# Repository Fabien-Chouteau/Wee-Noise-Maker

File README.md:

The [PGB-1 Firmware is now hosted on a different repo](https://github.com/wee-noise-makers/WNM-PGB1-firmware).

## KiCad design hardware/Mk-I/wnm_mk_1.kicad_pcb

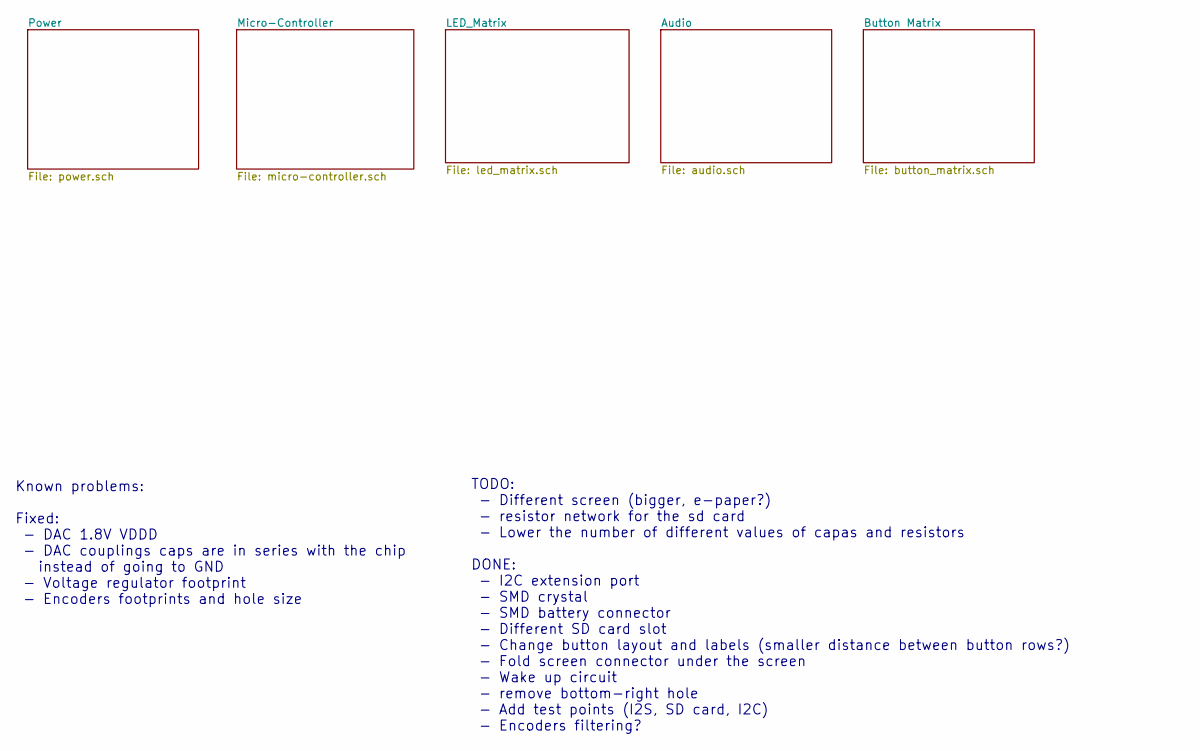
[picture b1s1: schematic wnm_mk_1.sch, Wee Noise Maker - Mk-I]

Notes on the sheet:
TODO: - Different screen (bigger, e-paper?) - resistor network for the sd card - Lower the number of different values of capas and resistors DONE: - I2C extension port - SMD crystal - SMD battery connector - Different SD card slot - Change button layout and labels (smaller distance between button r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
Known problems: Fixed: - DAC 1.8V VDDD - DAC couplings caps are in series with the chip instead of going to GND - Voltage regulator footprint - Encoders footprints and hole size

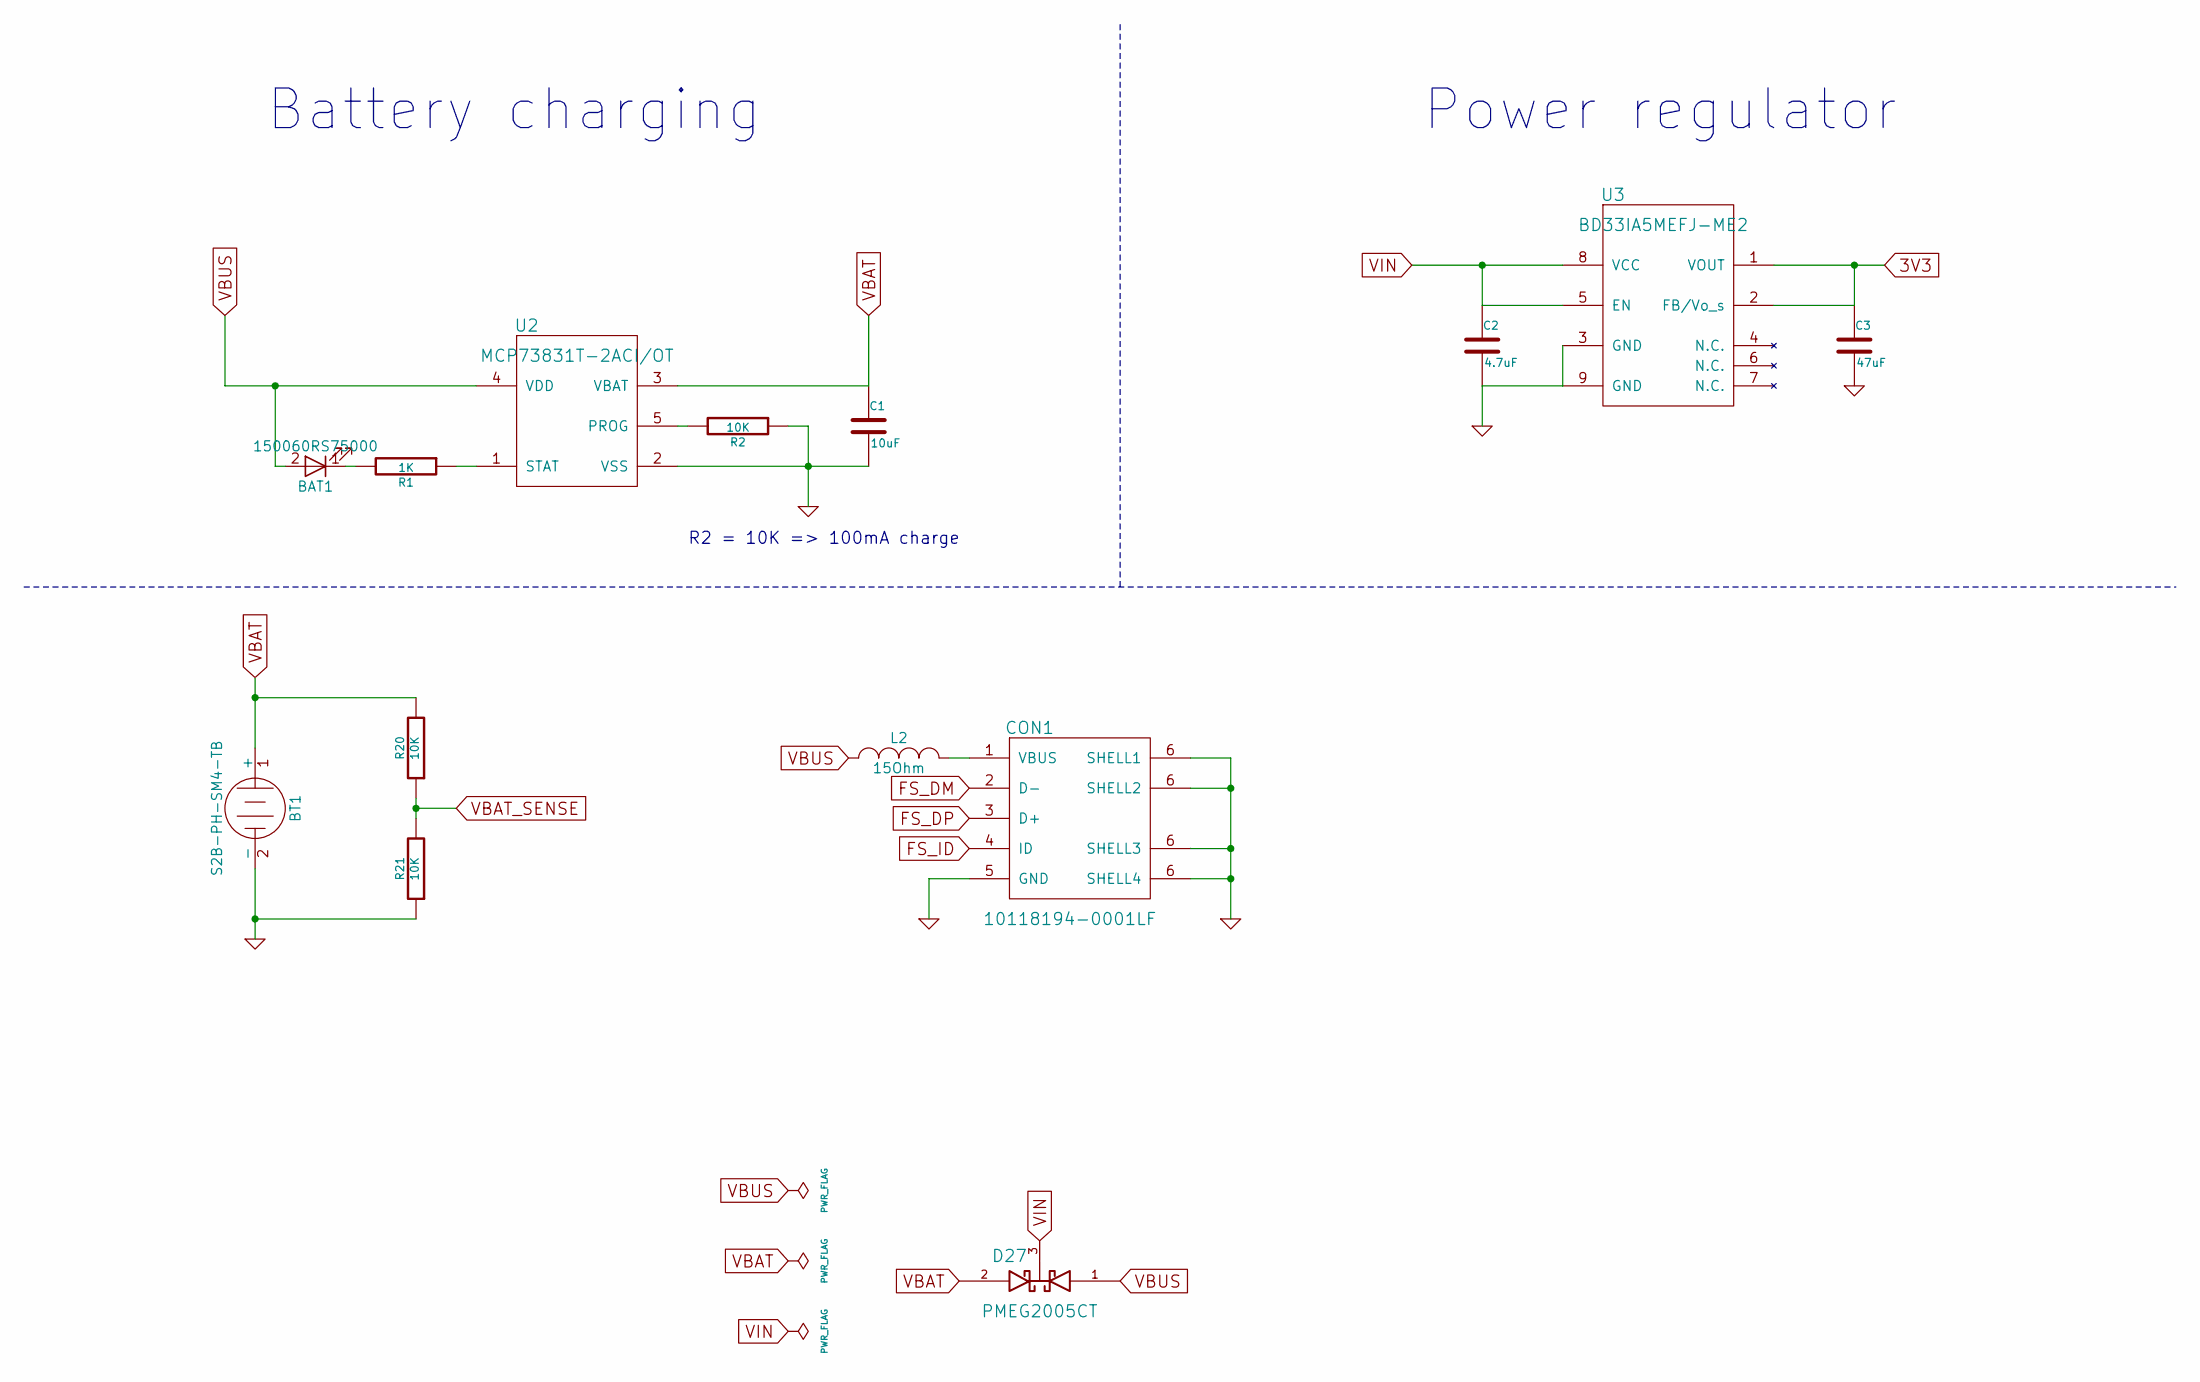
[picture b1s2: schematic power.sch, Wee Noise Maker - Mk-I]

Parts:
BAT1: 150060RS75000; LED_0805
BT1: S2B-PH-SM4-TB; JST_PH_S2B-PH-SM4-TB_02x2.00mm_Angled
C1: 10uF; C_0805
C2: 4.7uF; C_0805
C3: 47uF; C_1206
CON1: 10118194-0001LF; USB_Micro-B
D27: PMEG2005CT; SOT-23
L2: 15Ohm; C_0805
R1: 1K; R_0805
R2, R20, R21: 10K; R_0805
U2: MCP73831T-2ACI/OT; SOT-23-5
U3: BD33IA5MEFJ-ME2; HTSOP-J8

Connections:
3V3: C3.1, U3.1 (VOUT), U3.2 (FB/Vo_s); also elsewhere on the board
FS_DM: CON1.2 (D-); also elsewhere on the board
FS_DP: CON1.3 (D+); also elsewhere on the board
FS_ID: CON1.4 (ID); also elsewhere on the board
GND: BT1.2 (-), C1.2, C2.2, C3.2, CON1.5 (GND), CON1.6 (SHELL1), R2.1, R21.1, U2.2 (VSS), U3.3 (GND), U3.9 (GND); also elsewhere on the board
unnamed: BAT1.1 (K), R1.2
unnamed: CON1.1 (VBUS), L2.2
unnamed: R1.1, U2.1 (STAT)
unnamed: R2.2, U2.5 (PROG)
VBAT: BT1.1 (+), C1.1, D27.2 (anode), R20.2, U2.3 (VBAT)
VBAT_SENSE: R20.1, R21.2; also elsewhere on the board
VBUS: BAT1.2 (A), D27.1 (Anode), L2.1, U2.4 (VDD); also elsewhere on the board
VIN: C2.1, D27.3 (cathode), U3.5 (EN), U3.8 (VCC)

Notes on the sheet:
Battery charging
Power regulator
R2 = 10K => 100mA charge

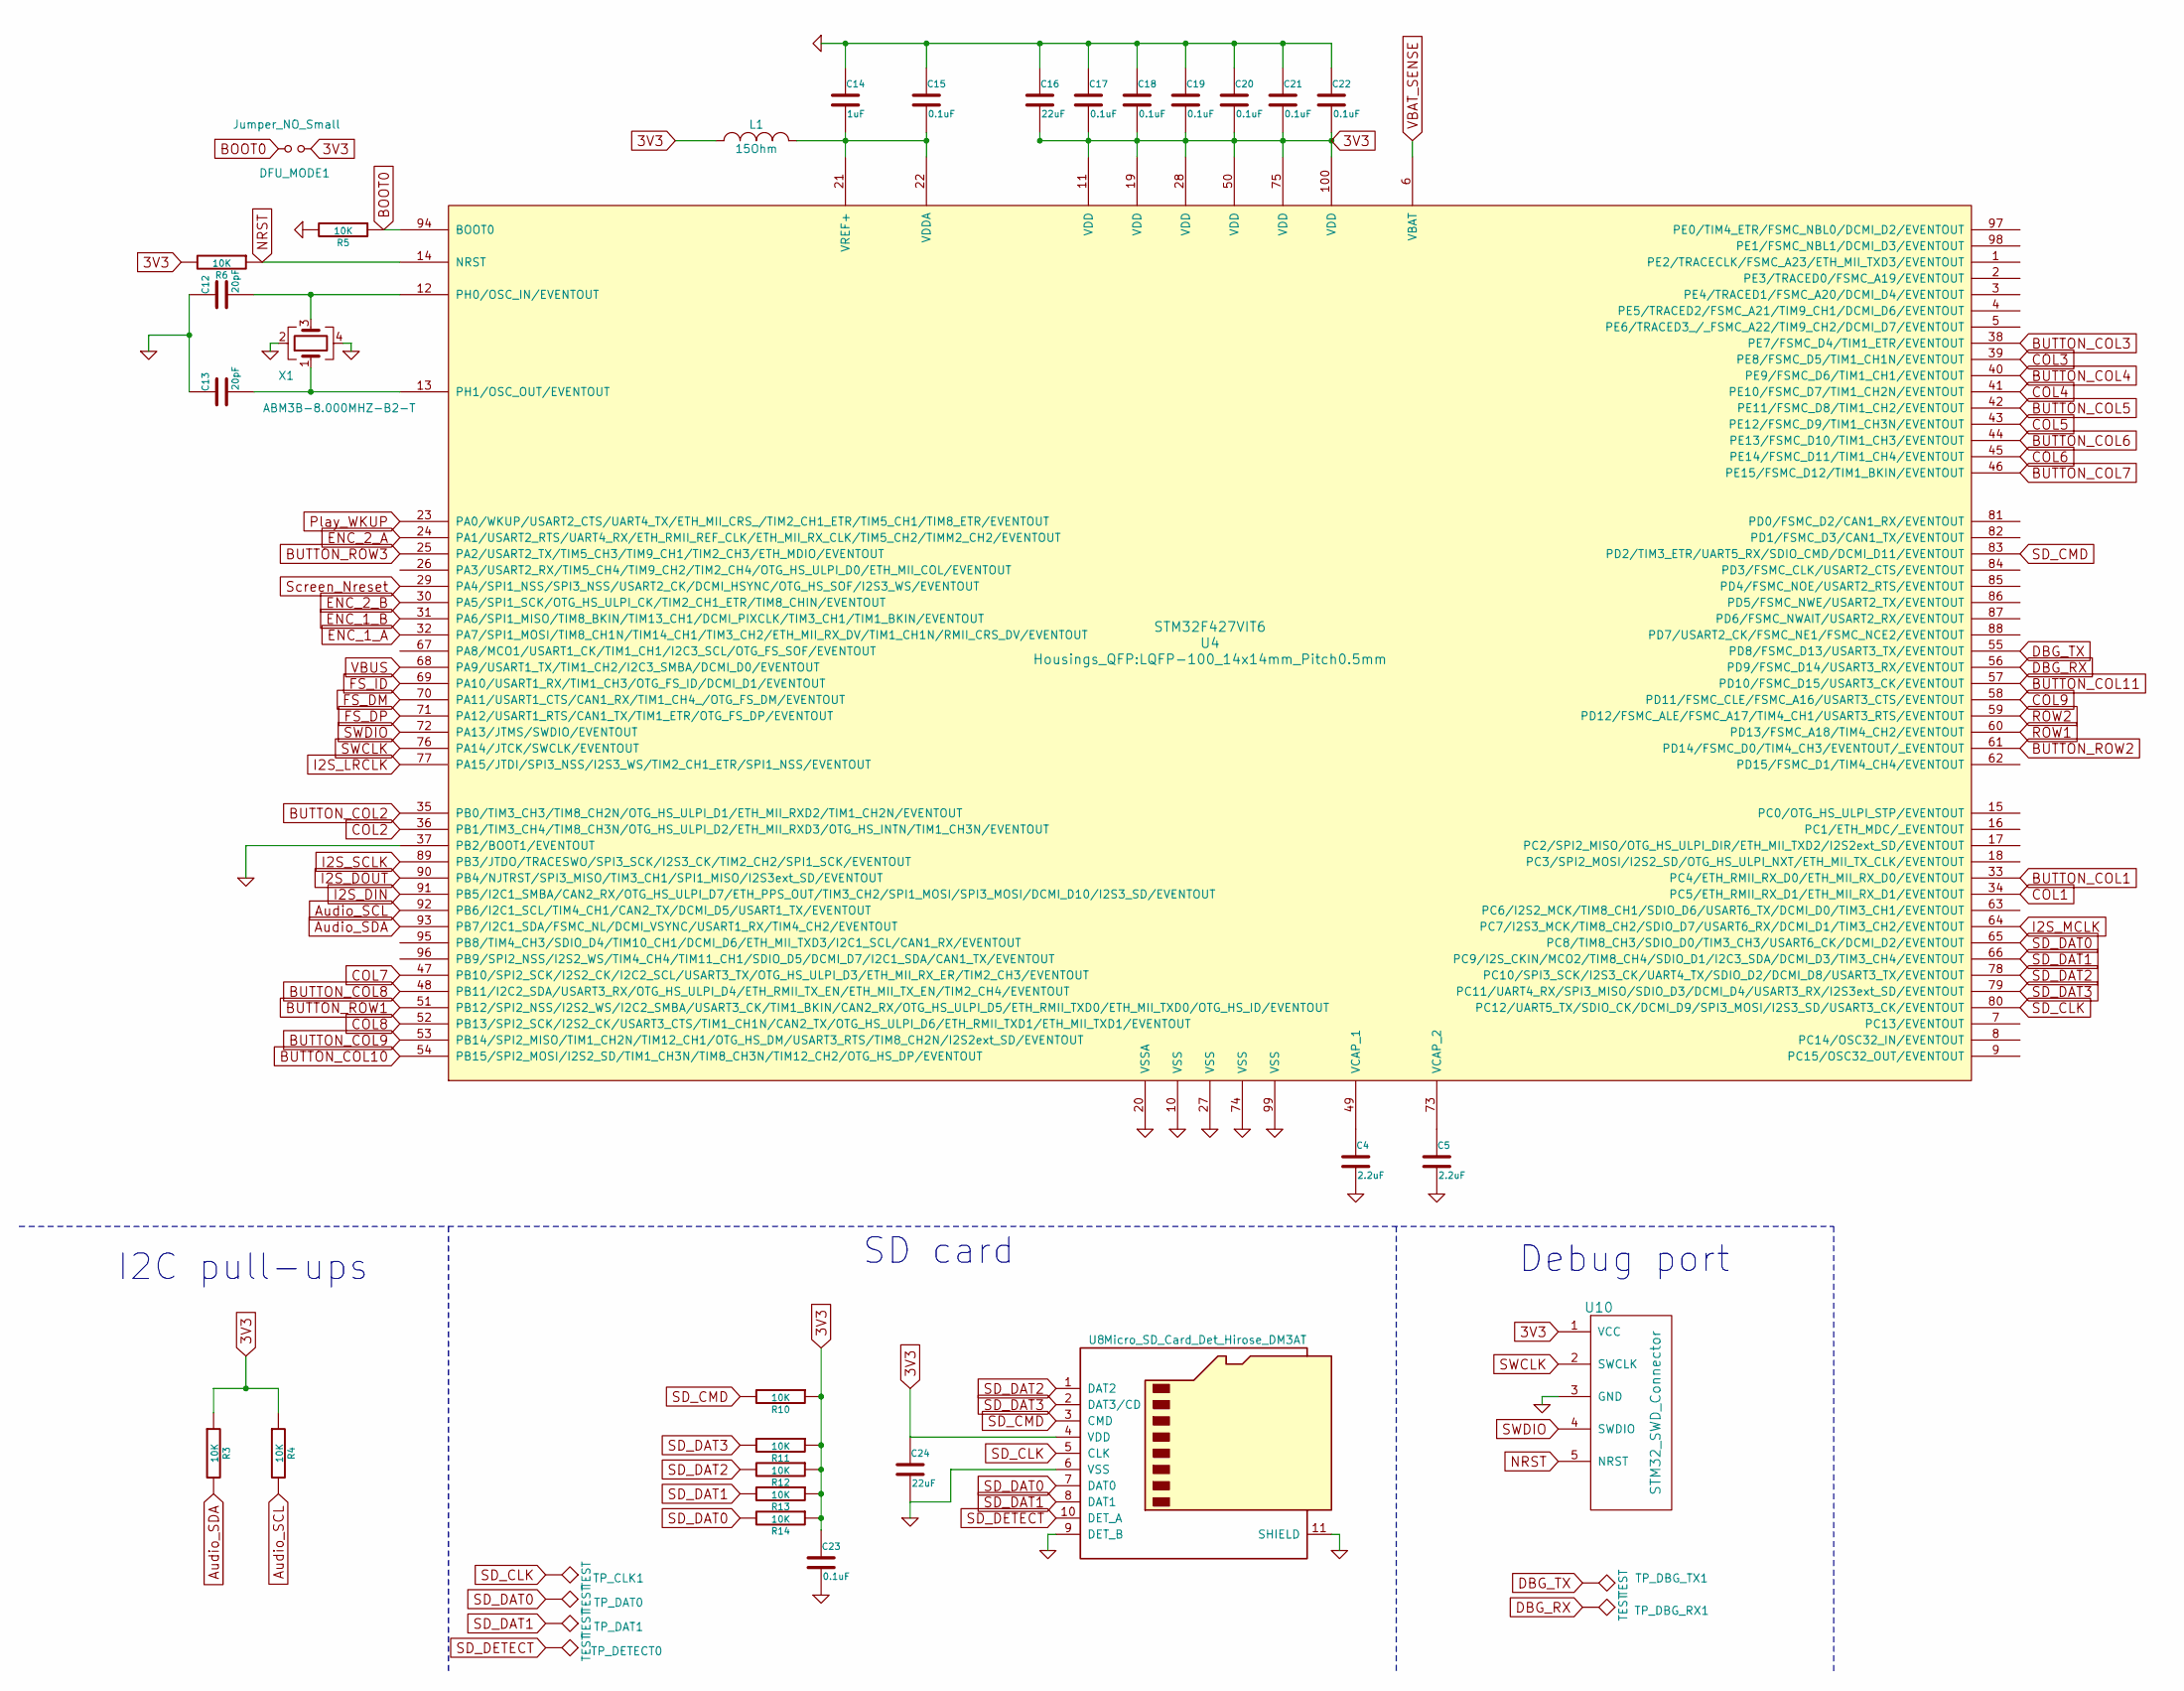
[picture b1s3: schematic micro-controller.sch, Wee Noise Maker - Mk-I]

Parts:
C4, C5: 2.2uF; C_0805
C12, C13: 20pF; C_0805
C14: 1uF; C_0805
C15, C17, C18, C19, C20, C21, C22, C23: 0.1uF; C_0805
C16, C24: 22uF; C_0805
DFU_MODE1: Jumper_NO_Small; SW_SPST_EVQP7A
L1: 15Ohm; C_0805
R3, R4, R5, R6, R10, R11, R12, R13, R14: 10K; R_0805
TP_CLK1: TEST; Measurement_Point_Round-SMD-Pad_Small
TP_DAT0, TP_DAT1: TEST; Measurement_Point_Round-SMD-Pad_Small
TP_DBG_RX1: TEST; Measurement_Point_Round-SMD-Pad_Small
TP_DBG_TX1: TEST; Measurement_Point_Round-SMD-Pad_Small
TP_DETECT0: TEST; Measurement_Point_Round-SMD-Pad_Small
U4: STM32F427VIT6; LQFP-100_14x14mm_Pitch0.5mm
U8: Micro_SD_Card_Det_Hirose_DM3AT; DM3D
U10: STM32_SWD_Connector; STM32_SWD_Connector_SMD
X1: ABM3B-8.000MHZ-B2-T; Crystal_SMD_0603_4Pads

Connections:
3V3: C16.2, C17.2, C18.2, C19.2, C20.2, C21.2, C22.2, C23.1, C24.1, DFU_MODE1.1, L1.1, R3.1, R4.1, R6.2, R10.1, R11.1, R12.1, R13.1, R14.1, U4.11 (VDD), U4.19 (VDD), U4.28 (VDD), U4.50 (VDD), U4.75 (VDD), U4.100 (VDD), U8.4 (VDD), U10.1 (VCC); also elsewhere on the board
Audio_SCL: R4.2, U4.92 (PB6/I2C1_SCL/TIM4_CH1/CAN2_TX/DCMI_D5/U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); also elsewhere on the board
Audio_SDA: R3.2, U4.93 (PB7/I2C1_SDA/FSMC_NL/DCMI_VSYNC/USART1_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); also elsewhere on the board
BOOT0: DFU_MODE1.2, R5.1, U4.94 (BOOT0)
BUTTON_COL1: U4.33 (PC4/ETH_RMII_RX_D0/ETH_MII_RX_D0/EVENTO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); also elsewhere on the board
BUTTON_COL2: U4.35 (PB0/TIM3_CH3/TIM8_CH2N/OTG_HS_ULPI_D1/E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); also elsewhere on the board
BUTTON_COL3: U4.38 (PE7/FSMC_D4/TIM1_ETR/EVENTOUT); also elsewhere on the board
BUTTON_COL4: U4.40 (PE9/FSMC_D6/TIM1_CH1/EVENTOUT); also elsewhere on the board
BUTTON_COL5: U4.42 (PE11/FSMC_D8/TIM1_CH2/EVENTOUT); also elsewhere on the board
BUTTON_COL6: U4.44 (PE13/FSMC_D10/TIM1_CH3/EVENTOUT); also elsewhere on the board
BUTTON_COL7: U4.46 (PE15/FSMC_D12/TIM1_BKIN/EVENTOUT); also elsewhere on the board
BUTTON_COL8: U4.48 (PB11/I2C2_SDA/USART3_RX/OTG_HS_ULPI_D4/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); also elsewhere on the board
BUTTON_COL9: U4.53 (PB14/SPI2_MISO/TIM1_CH2N/TIM12_CH1/OTG_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); also elsewhere on the board
BUTTON_COL10: U4.54 (PB15/SPI2_MOSI/I2S2_SD/TIM1_CH3N/TIM8_C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); also elsewhere on the board
BUTTON_COL11: U4.57 (PD10/FSMC_D15/USART3_CK/EVENTOUT); also elsewhere on the board
BUTTON_ROW1: U4.51 (PB12/SPI2_NSS/I2S2_WS/I2C2_SMBA/USART3_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); also elsewhere on the board
BUTTON_ROW2: U4.61 (PD14/FSMC_D0/TIM4_CH3/EVENTOUT/_EVENTOUT); also elsewhere on the board
BUTTON_ROW3: U4.25 (PA2/USART2_TX/TIM5_CH3/TIM9_CH1/TIM2_CH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); also elsewhere on the board
COL1: U4.34 (PC5/ETH_RMII_RX_D1/ETH_MII_RX_D1/EVENTO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); also elsewhere on the board
COL2: U4.36 (PB1/TIM3_CH4/TIM8_CH3N/OTG_HS_ULPI_D2/E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); also elsewhere on the board
COL3: U4.39 (PE8/FSMC_D5/TIM1_CH1N/EVENTOUT); also elsewhere on the board
COL4: U4.41 (PE10/FSMC_D7/TIM1_CH2N/EVENTOUT); also elsewhere on the board
COL5: U4.43 (PE12/FSMC_D9/TIM1_CH3N/EVENTOUT); also elsewhere on the board
COL6: U4.45 (PE14/FSMC_D11/TIM1_CH4/EVENTOUT); also elsewhere on the board
COL7: U4.47 (PB10/SPI2_SCK/I2S2_CK/I2C2_SCL/USART3_T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); also elsewhere on the board
COL8: U4.52 (PB13/SPI2_SCK/I2S2_CK/USART3_CTS/TIM1_C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); also elsewhere on the board
COL9: U4.58 (PD11/FSMC_CLE/FSMC_A16/USART3_CTS/EVENT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); also elsewhere on the board
DBG_RX: TP_DBG_RX1.1, U4.56 (PD9/FSMC_D14/USART3_RX/EVENTOUT)
DBG_TX: TP_DBG_TX1.1, U4.55 (PD8/FSMC_D13/USART3_TX/EVENTOUT)
ENC_1_A: U4.32 (PA7/SPI1_MOSI/TIM8_CH1N/TIM14_CH1/TIM3_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); also elsewhere on the board
ENC_1_B: U4.31 (PA6/SPI1_MISO/TIM8_BKIN/TIM13_CH1/DCMI_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); also elsewhere on the board
ENC_2_A: U4.24 (PA1/USART2_RTS/UART4_RX/ETH_RMII_REF_CL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); also elsewhere on the board
ENC_2_B: U4.30 (PA5/SPI1_SCK/OTG_HS_ULPI_CK/TIM2_CH1_ET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); also elsewhere on the board
FS_DM: U4.70 (PA11/USART1_CTS/CAN1_RX/TIM1_CH4_/OTG_F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); also elsewhere on the board
FS_DP: U4.71 (PA12/USART1_RTS/CAN1_TX/TIM1_ETR/OTG_FS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); also elsewhere on the board
FS_ID: U4.69 (PA10/USART1_RX/TIM1_CH3/OTG_FS_ID/DCMI_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); also elsewhere on the board
GND: C4.2, C5.2, C12.1, C13.1, C14.1, C15.1, C16.1, C17.1, C18.1, C19.1, C20.1, C21.1, C22.1, C23.2, C24.2, R5.2, U4.10 (VSS), U4.20 (VSSA), U4.27 (VSS), U4.37 (PB2/BOOT1/EVENTOUT), U4.74 (VSS), U4.99 (VSS), U8.6 (VSS), U8.9 (DET_B), U8.11 (SHIELD), U10.3 (GND), X1.2, X1.4; also elsewhere on the board
I2S_DIN: U4.91 (PB5/I2C1_SMBA/CAN2_RX/OTG_HS_ULPI_D7/ET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); also elsewhere on the board
I2S_DOUT: U4.90 (PB4/NJTRST/SPI3_MISO/TIM3_CH1/SPI1_MISO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); also elsewhere on the board
I2S_LRCLK: U4.77 (PA15/JTDI/SPI3_NSS/I2S3_WS/TIM2_CH1_ETR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); also elsewhere on the board
I2S_MCLK: U4.64 (PC7/I2S3_MCK/TIM8_CH2/SDIO_D7/USART6_RX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); also elsewhere on the board
I2S_SCLK: U4.89 (PB3/JTDO/TRACESWO/SPI3_SCK/I2S3_CK/TIM2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); also elsewhere on the board
NRST: R6.1, U4.14 (NRST), U10.5 (NRST)
unnamed: C4.1, U4.49 (VCAP_1)
unnamed: C5.1, U4.73 (VCAP_2)
unnamed: C12.2, U4.12 (PH0/OSC_IN/EVENTOUT), X1.3
unnamed: C13.2, U4.13 (PH1/OSC_OUT/EVENTOUT), X1.1
unnamed: C14.2, C15.2, L1.2, U4.21 (VREF+), U4.22 (VDDA)
Play_WKUP: U4.23 (PA0/WKUP/USART2_CTS/UART4_TX/ETH_MII_CR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); also elsewhere on the board
ROW1: U4.60 (PD13/FSMC_A18/TIM4_CH2/EVENTOUT); also elsewhere on the board
ROW2: U4.59 (PD12/FSMC_ALE/FSMC_A17/TIM4_CH1/USART3_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); also elsewhere on the board
SD_CLK: TP_CLK1.1, U4.80 (PC12/UART5_TX/SDIO_CK/DCMI_D9/SPI3_MOSI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), U8.5 (CLK)
SD_CMD: R10.2, U4.83 (PD2/TIM3_ETR/UART5_RX/SDIO_CMD/DCMI_D11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), U8.3 (CMD); also elsewhere on the board
SD_DAT0: R14.2, TP_DAT0.1, U4.65 (PC8/TIM8_CH3/SDIO_D0/TIM3_CH3/USART6_CK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), U8.7 (DAT0)
SD_DAT1: R13.2, TP_DAT1.1, U4.66 (PC9/I2S_CKIN/MCO2/TIM8_CH4/SDIO_D1/I2C3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), U8.8 (DAT1)
SD_DAT2: R12.2, U4.78 (PC10/SPI3_SCK/I2S3_CK/UART4_TX/SDIO_D2/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), U8.1 (DAT2); also elsewhere on the board
SD_DAT3: R11.2, U4.79 (PC11/UART4_RX/SPI3_MISO/SDIO_D3/DCMI_D4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), U8.2 (DAT3/CD); also elsewhere on the board
SD_DETECT: TP_DETECT0.1, U8.10 (DET_A)
SWCLK: U4.76 (PA14/JTCK/SWCLK/EVENTOUT), U10.2 (SWCLK)
SWDIO: U4.72 (PA13/JTMS/SWDIO/EVENTOUT), U10.4 (SWDIO)
Screen_Nreset: U4.29 (PA4/SPI1_NSS/SPI3_NSS/USART2_CK/DCMI_HS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); also elsewhere on the board
VBAT_SENSE: U4.6 (VBAT); also elsewhere on the board
VBUS: U4.68 (PA9/USART1_TX/TIM1_CH2/I2C3_SMBA/DCMI_D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); also elsewhere on the board

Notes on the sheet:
I2C pull-ups
SD card
Debug port

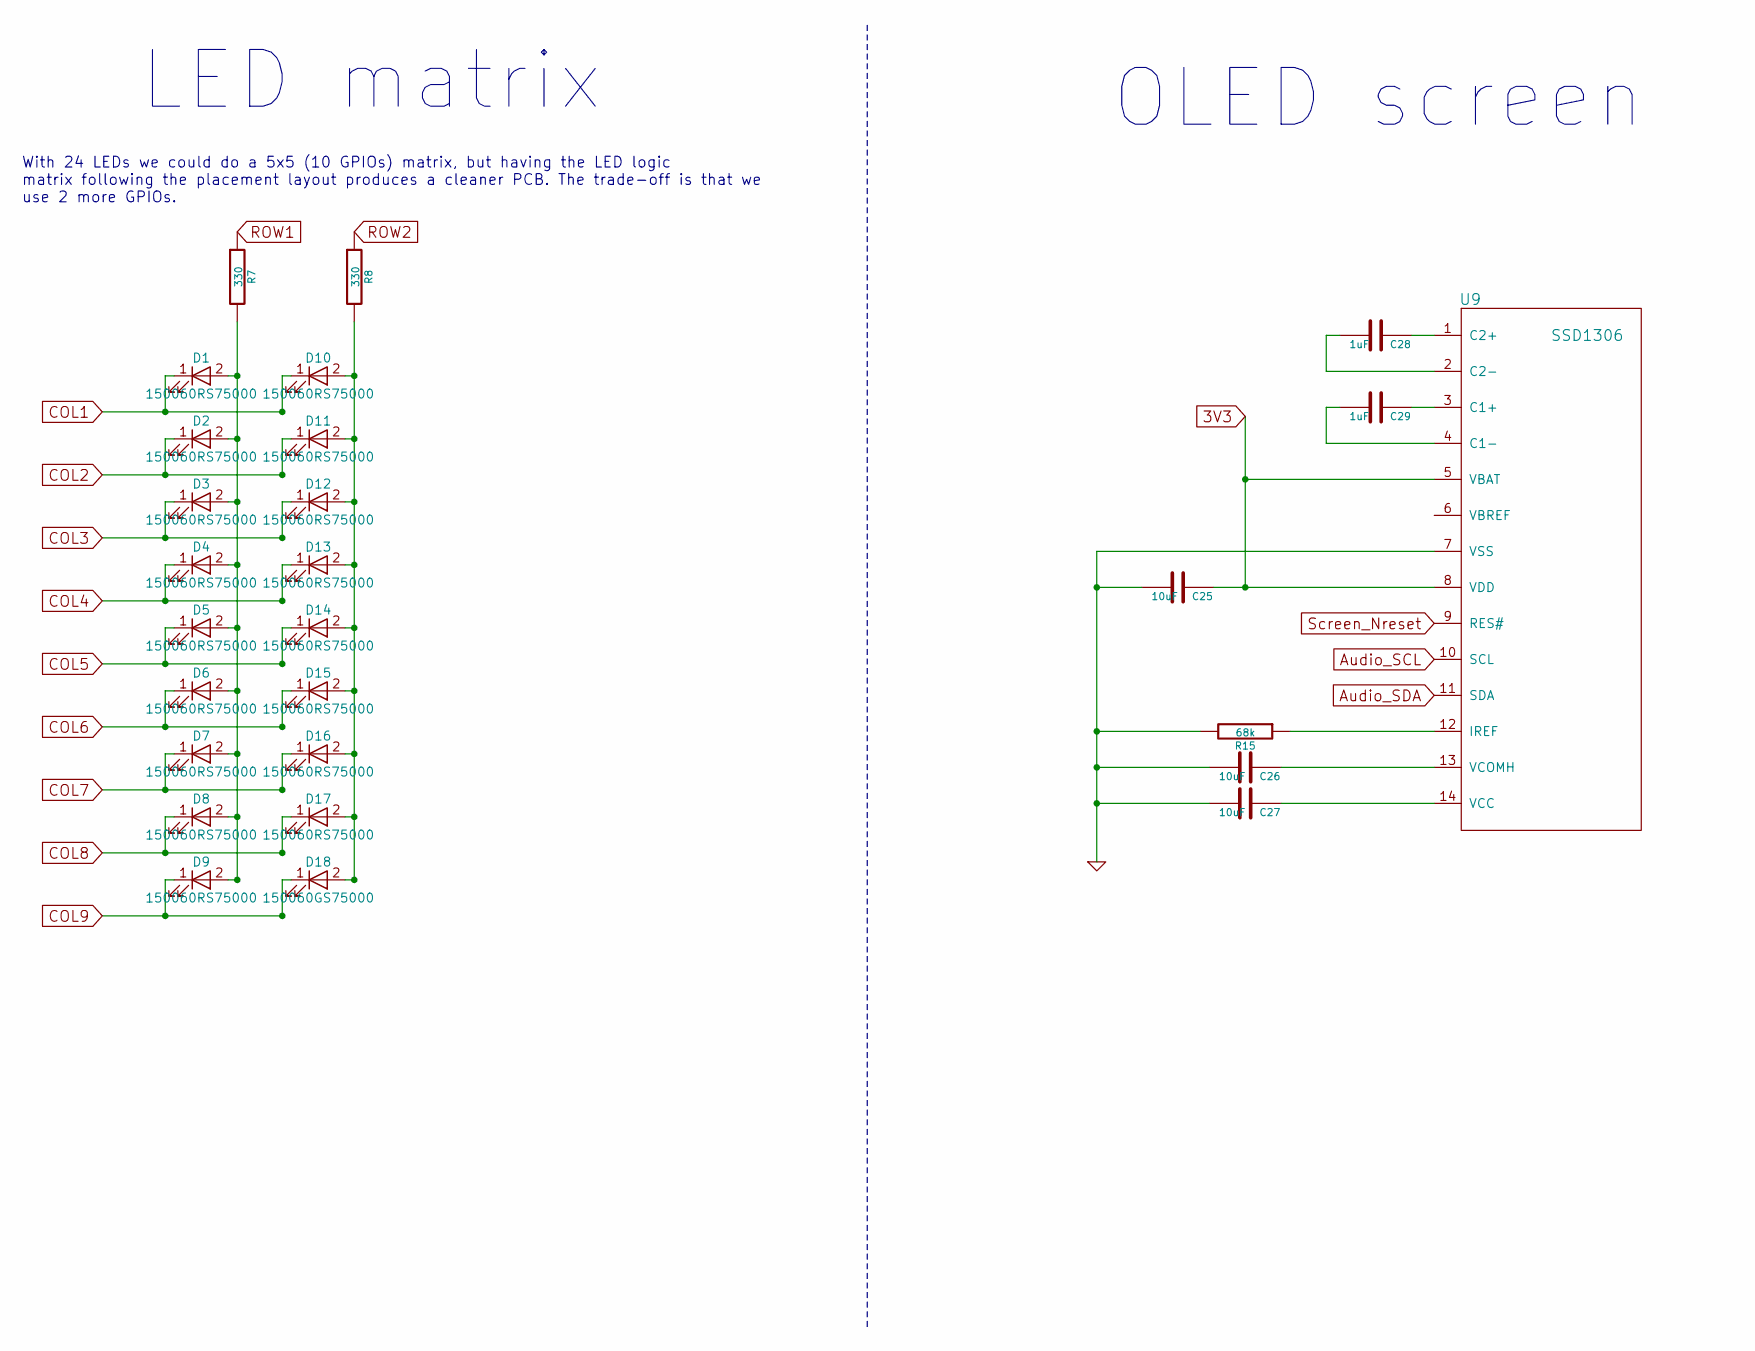
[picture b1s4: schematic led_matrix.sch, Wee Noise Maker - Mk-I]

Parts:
C25, C26, C27: 10uF; C_0805
C28, C29: 1uF; C_0805
D1, D2, D3, D4, D5, D6, D7, D8, D9, D10, D11, D12, D13, D14, D15, D16, D17: 150060RS75000; LED_0805
D18: 150060GS75000; LED_0805
R7, R8: 330; R_0805
R15: 68k; R_0805
U9: SSD1306; MIDAS_MCOT096016AV_OLED

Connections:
3V3: C25.1, U9.5 (VBAT), U9.8 (VDD); also elsewhere on the board
Audio_SCL: U9.10 (SCL); also elsewhere on the board
Audio_SDA: U9.11 (SDA); also elsewhere on the board
COL1: D1.1 (K), D10.1 (K); also elsewhere on the board
COL2: D2.1 (K), D11.1 (K); also elsewhere on the board
COL3: D3.1 (K), D12.1 (K); also elsewhere on the board
COL4: D4.1 (K), D13.1 (K); also elsewhere on the board
COL5: D5.1 (K), D14.1 (K); also elsewhere on the board
COL6: D6.1 (K), D15.1 (K); also elsewhere on the board
COL7: D7.1 (K), D16.1 (K); also elsewhere on the board
COL8: D8.1 (K), D17.1 (K); also elsewhere on the board
COL9: D9.1 (K), D18.1 (K); also elsewhere on the board
GND: C25.2, C26.2, C27.2, R15.2, U9.7 (VSS); also elsewhere on the board
unnamed: C26.1, U9.13 (VCOMH)
unnamed: C27.1, U9.14 (VCC)
unnamed: C28.1, U9.1 (C2+)
unnamed: C28.2, U9.2 (C2-)
unnamed: C29.1, U9.3 (C1+)
unnamed: C29.2, U9.4 (C1-)
unnamed: D1.2 (A), D2.2 (A), D3.2 (A), D4.2 (A), D5.2 (A), D6.2 (A), D7.2 (A), D8.2 (A), D9.2 (A), R7.2
unnamed: D10.2 (A), D11.2 (A), D12.2 (A), D13.2 (A), D14.2 (A), D15.2 (A), D16.2 (A), D17.2 (A), D18.2 (A), R8.2
unnamed: R15.1, U9.12 (IREF)
ROW1: R7.1; also elsewhere on the board
ROW2: R8.1; also elsewhere on the board
Screen_Nreset: U9.9 (RES#); also elsewhere on the board

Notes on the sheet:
With 24 LEDs we could do a 5x5 (10 GPIOs) matrix, but having the LED logic matrix following the placement layout produces a cleaner PCB. The trade-off is that we use 2 more GPIOs.
LED matrix
OLED screen

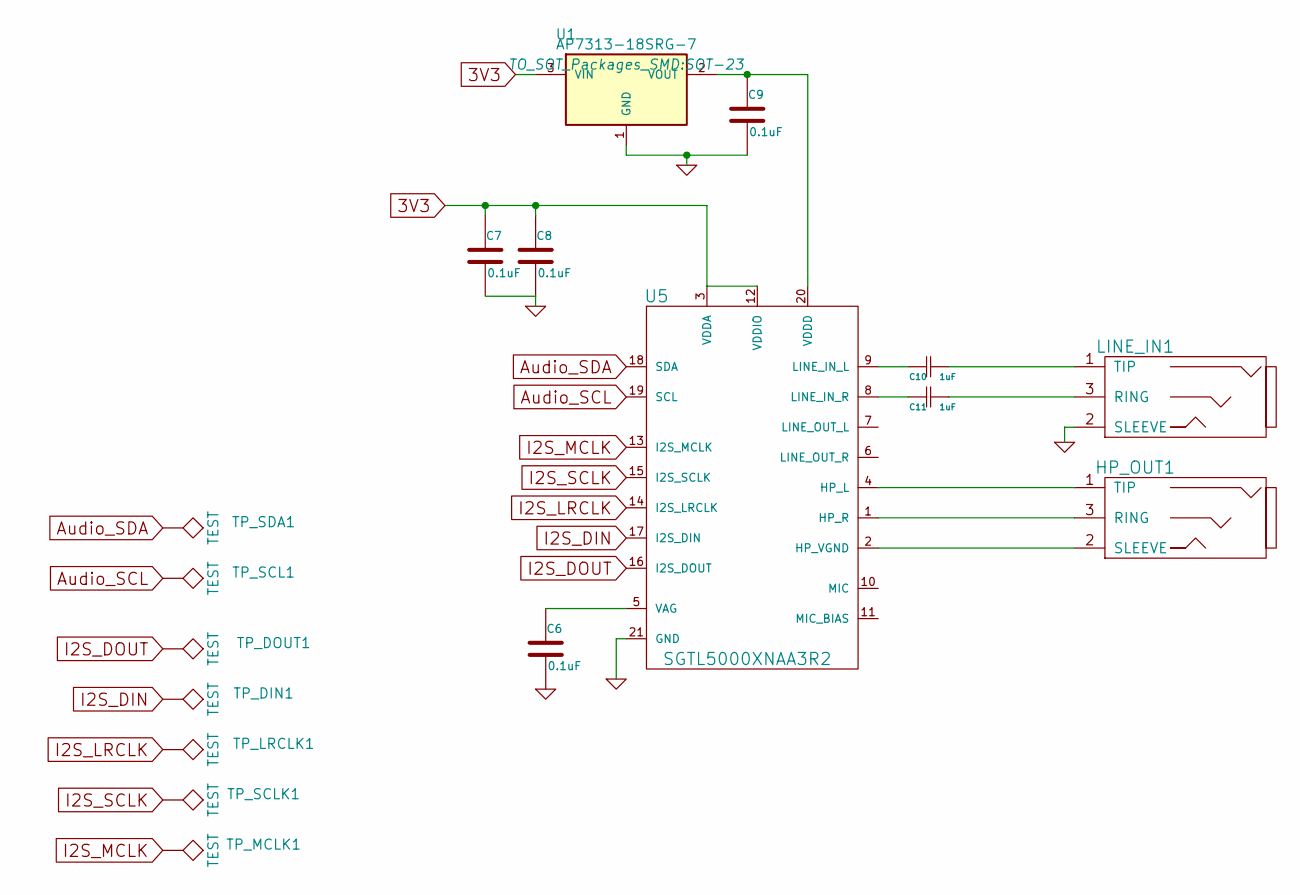
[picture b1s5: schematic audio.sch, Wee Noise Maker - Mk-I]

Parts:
C6, C7, C8, C9: 0.1uF; C_0805
C10, C11: 1uF; C_0805
HP_OUT1: SJ-3523-SMT
LINE_IN1: SJ-3523-SMT
TP_DIN1: TEST; Measurement_Point_Round-SMD-Pad_Small
TP_DOUT1: TEST; Measurement_Point_Round-SMD-Pad_Small
TP_LRCLK1: TEST; Measurement_Point_Round-SMD-Pad_Small
TP_MCLK1: TEST; Measurement_Point_Round-SMD-Pad_Small
TP_SCL1: TEST; Measurement_Point_Round-SMD-Pad_Small
TP_SCLK1: TEST; Measurement_Point_Round-SMD-Pad_Small
TP_SDA1: TEST; Measurement_Point_Round-SMD-Pad_Small
U1: AP7313-18SRG-7; SOT-23
U5: SGTL5000XNAA3R2; UQFN-20-1EP_3x3mm_Pitch0.4mm

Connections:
3V3: C7.1, C8.1, U1.3 (VIN), U5.3 (VDDA), U5.12 (VDDIO); also elsewhere on the board
Audio_SCL: TP_SCL1.1, U5.19 (SCL); also elsewhere on the board
Audio_SDA: TP_SDA1.1, U5.18 (SDA); also elsewhere on the board
GND: C6.2, C7.2, C8.2, C9.2, LINE_IN1.2 (SLEEVE), U1.1 (GND), U5.21 (GND); also elsewhere on the board
I2S_DIN: TP_DIN1.1, U5.17 (I2S_DIN); also elsewhere on the board
I2S_DOUT: TP_DOUT1.1, U5.16 (I2S_DOUT); also elsewhere on the board
I2S_LRCLK: TP_LRCLK1.1, U5.14 (I2S_LRCLK); also elsewhere on the board
I2S_MCLK: TP_MCLK1.1, U5.13 (I2S_MCLK); also elsewhere on the board
I2S_SCLK: TP_SCLK1.1, U5.15 (I2S_SCLK); also elsewhere on the board
unnamed: C6.1, U5.5 (VAG)
unnamed: C9.1, U1.2 (VOUT), U5.20 (VDDD)
unnamed: C10.1, LINE_IN1.1 (TIP)
unnamed: C10.2, U5.9 (LINE_IN_L)
unnamed: C11.1, LINE_IN1.3 (RING)
unnamed: C11.2, U5.8 (LINE_IN_R)
unnamed: HP_OUT1.1 (TIP), U5.4 (HP_L)
unnamed: HP_OUT1.2 (SLEEVE), U5.2 (HP_VGND)
unnamed: HP_OUT1.3 (RING), U5.1 (HP_R)

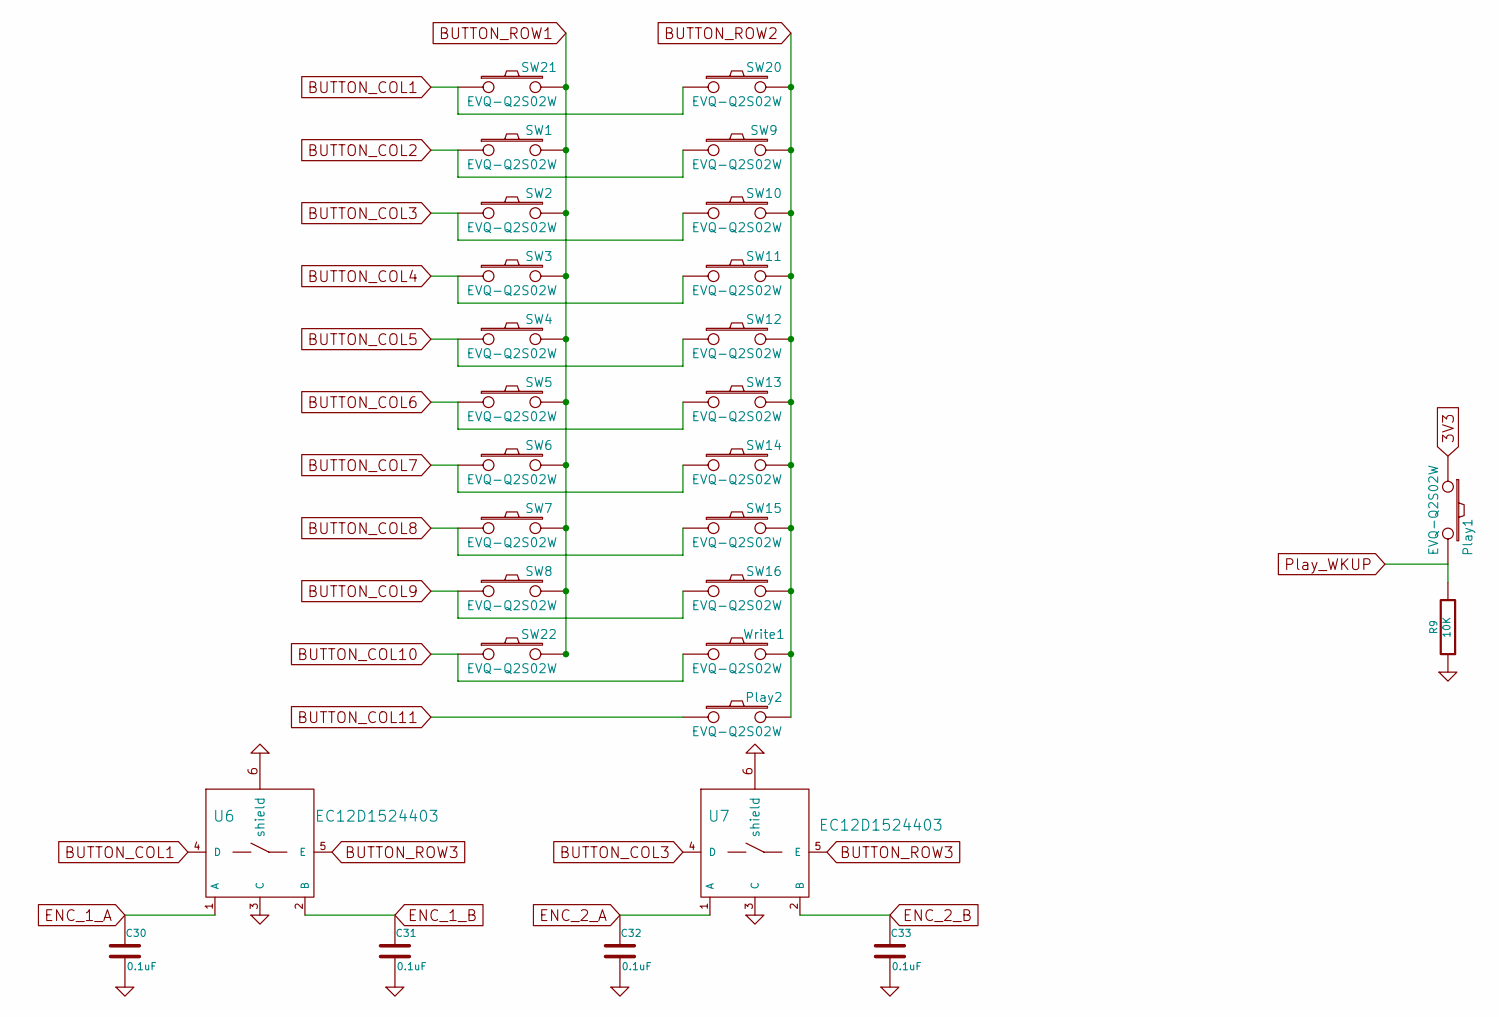
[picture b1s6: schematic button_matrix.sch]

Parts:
C30, C31, C32, C33: 0.1uF; C_0805
Play1, Play2: EVQ-Q2S02W; SW_SPST_B3SL-1002P
R9: 10K; R_0805
SW1, SW2, SW3, SW4, SW5, SW6, SW7, SW8, SW9, SW10, SW11, SW12, SW13, SW14, SW15, SW16, SW20, SW21, SW22: EVQ-Q2S02W; SW_SPST_B3SL-1002P
U6, U7: EC12D1524403; encoder_EC12D
Write1: EVQ-Q2S02W; SW_SPST_B3SL-1002P

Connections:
3V3: Play1.1; also elsewhere on the board
BUTTON_COL1: SW20.1, SW21.1, U6.4 (D); also elsewhere on the board
BUTTON_COL2: SW1.1, SW9.1; also elsewhere on the board
BUTTON_COL3: SW2.1, SW10.1, U7.4 (D); also elsewhere on the board
BUTTON_COL4: SW3.1, SW11.1; also elsewhere on the board
BUTTON_COL5: SW4.1, SW12.1; also elsewhere on the board
BUTTON_COL6: SW5.1, SW13.1; also elsewhere on the board
BUTTON_COL7: SW6.1, SW14.1; also elsewhere on the board
BUTTON_COL8: SW7.1, SW15.1; also elsewhere on the board
BUTTON_COL9: SW8.1, SW16.1; also elsewhere on the board
BUTTON_COL10: SW22.1, Write1.1; also elsewhere on the board
BUTTON_COL11: Play2.1; also elsewhere on the board
BUTTON_ROW1: SW1.2, SW2.2, SW3.2, SW4.2, SW5.2, SW6.2, SW7.2, SW8.2, SW21.2, SW22.2; also elsewhere on the board
BUTTON_ROW2: Play2.2, SW9.2, SW10.2, SW11.2, SW12.2, SW13.2, SW14.2, SW15.2, SW16.2, SW20.2, Write1.2; also elsewhere on the board
BUTTON_ROW3: U6.5 (E), U7.5 (E); also elsewhere on the board
ENC_1_A: C30.1, U6.1 (A); also elsewhere on the board
ENC_1_B: C31.1, U6.2 (B); also elsewhere on the board
ENC_2_A: C32.1, U7.1 (A); also elsewhere on the board
ENC_2_B: C33.1, U7.2 (B); also elsewhere on the board
GND: C30.2, C31.2, C32.2, C33.2, R9.1, U6.3 (C), U6.6 (shield), U7.3 (C), U7.6 (shield); also elsewhere on the board
Play_WKUP: Play1.2, R9.2; also elsewhere on the board
